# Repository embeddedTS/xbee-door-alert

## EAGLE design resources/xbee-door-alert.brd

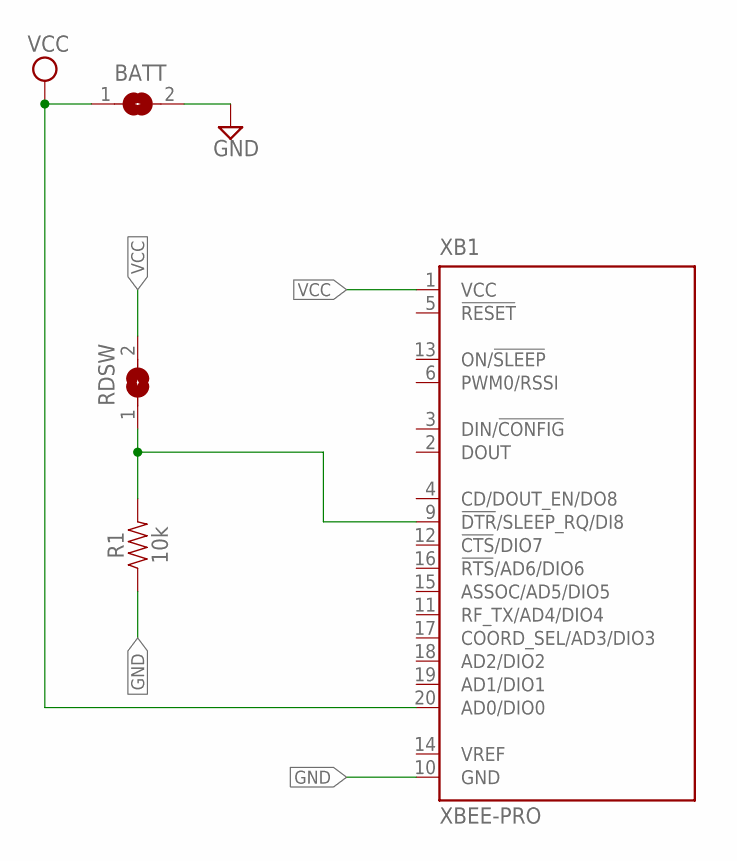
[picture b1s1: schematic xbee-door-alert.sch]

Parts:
BATT: SJW
R1: 10k; AXIAL-0.3
RDSW: SJW
XB1: XBEE-PRO

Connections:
GND: BATT.2, R1.P$1 (1), XB1.10 (GND)
SLEEP: R1.P$2 (2), RDSW.1, XB1.9 (!DTR!/SLEEP_RQ/DI8)
VCC: BATT.1, RDSW.2, XB1.1 (VCC), XB1.20 (AD0/DIO0)

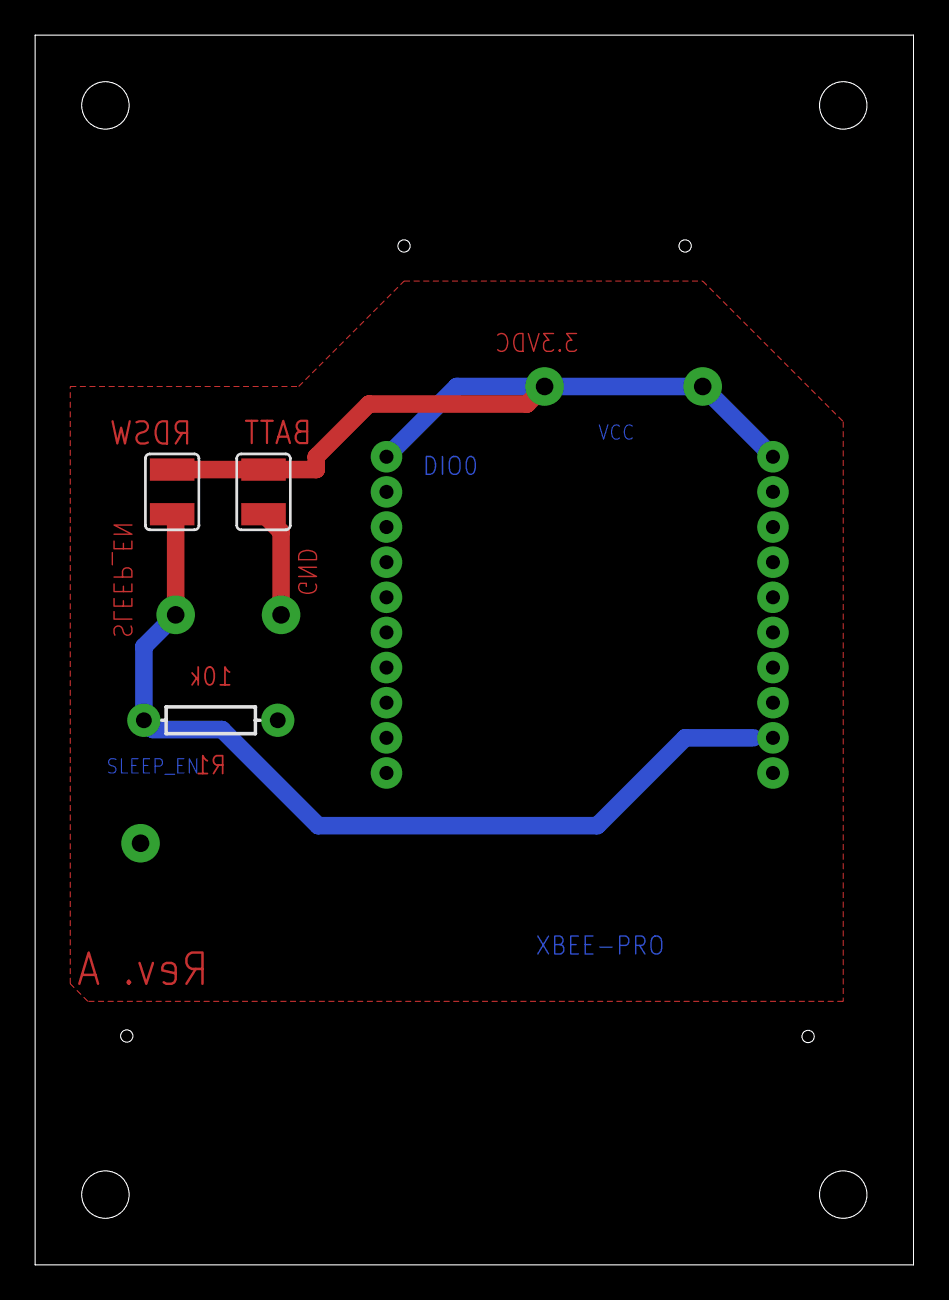
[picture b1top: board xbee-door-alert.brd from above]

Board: 2 copper layers, 50.0 x 70.0 mm, 4 parts (1 on the bottom side), 3 nets.

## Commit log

2017-10-09 Specify to address
2017-10-09 Add generic comments
2017-10-13 Consistent VCC and GND symbols

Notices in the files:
parts and their libraries:
SparkFun-Resistors: Licensing: Creative Commons ShareAlike 4.0 International - https://creativecommons.org/licenses/by-sa/4.0
